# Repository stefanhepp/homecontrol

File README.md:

HomeControl
===========

This is the sourcecode and plans for my home automation system.

Content
=======

- `homecontrol`: Sources and schematics for a simple AtMega based home automation controller with 8 24VDC digital inputs, 8 24VDC digital outputs (open collector), RS232 and 2 230VAC sense inputs.
- `pixtend`: Sources for the main controller, based on an PiXtend v2-S with Raspberry 3B, written in Python. Connects via RS232 and MQTT to the network.

Installation Pixtend OS
=======================

- Install Raspbian OS (64bit)
   - `sudo rpi-imager`: Enable SSH, set hostname, username, password
- Setup Rasbian, install software
  ```
  # Enable SPI, UART, console bootup, set locale
  sudo raspi-config
  sudo apt install vim screen git gpiod libgpiod-dev python3-dev python3-pip python3-paho-mqtt
  ```
- Install Pixtend Python library
  ```
  git clone https://git.kontron-electronics.de/sw/ked/raspberry-pi/pixtend-v2/pplv2.git
  cd pplv2
  git checkout 0.1.6-dev
  python setup.py bdist_wheel
  # Install into venv
  python -m venv ~/.venv
  source ~/.venv/bin/activate
  pip install dist/pixtendlibv2-0.1.6-py3-none-any.whl
  ```
- Install pixcontrol script
  ```
  # Install prerequisites
  . ~/.venv/bin/activate
  pip install pyserial paho-mqtt
  cd ~/homecontrol/pixtend
  sudo cp pixcontrol.service /etc/systemd/system/
  sudo systemctl enable pixcontrol
  ```

License
=======

This program is free software: you can redistribute it and/or modify
it under the terms of the GNU General Public License as published by
the Free Software Foundation, either version 3 of the License, or
(at your option) any later version.

This program is distributed in the hope that it will be useful,
but WITHOUT ANY WARRANTY; without even the implied warranty of
MERCHANTABILITY or FITNESS FOR A PARTICULAR PURPOSE.  See the
GNU General Public License for more details.

You should have received a copy of the GNU General Public License
along with this program.  If not, see <https://www.gnu.org/licenses/>.

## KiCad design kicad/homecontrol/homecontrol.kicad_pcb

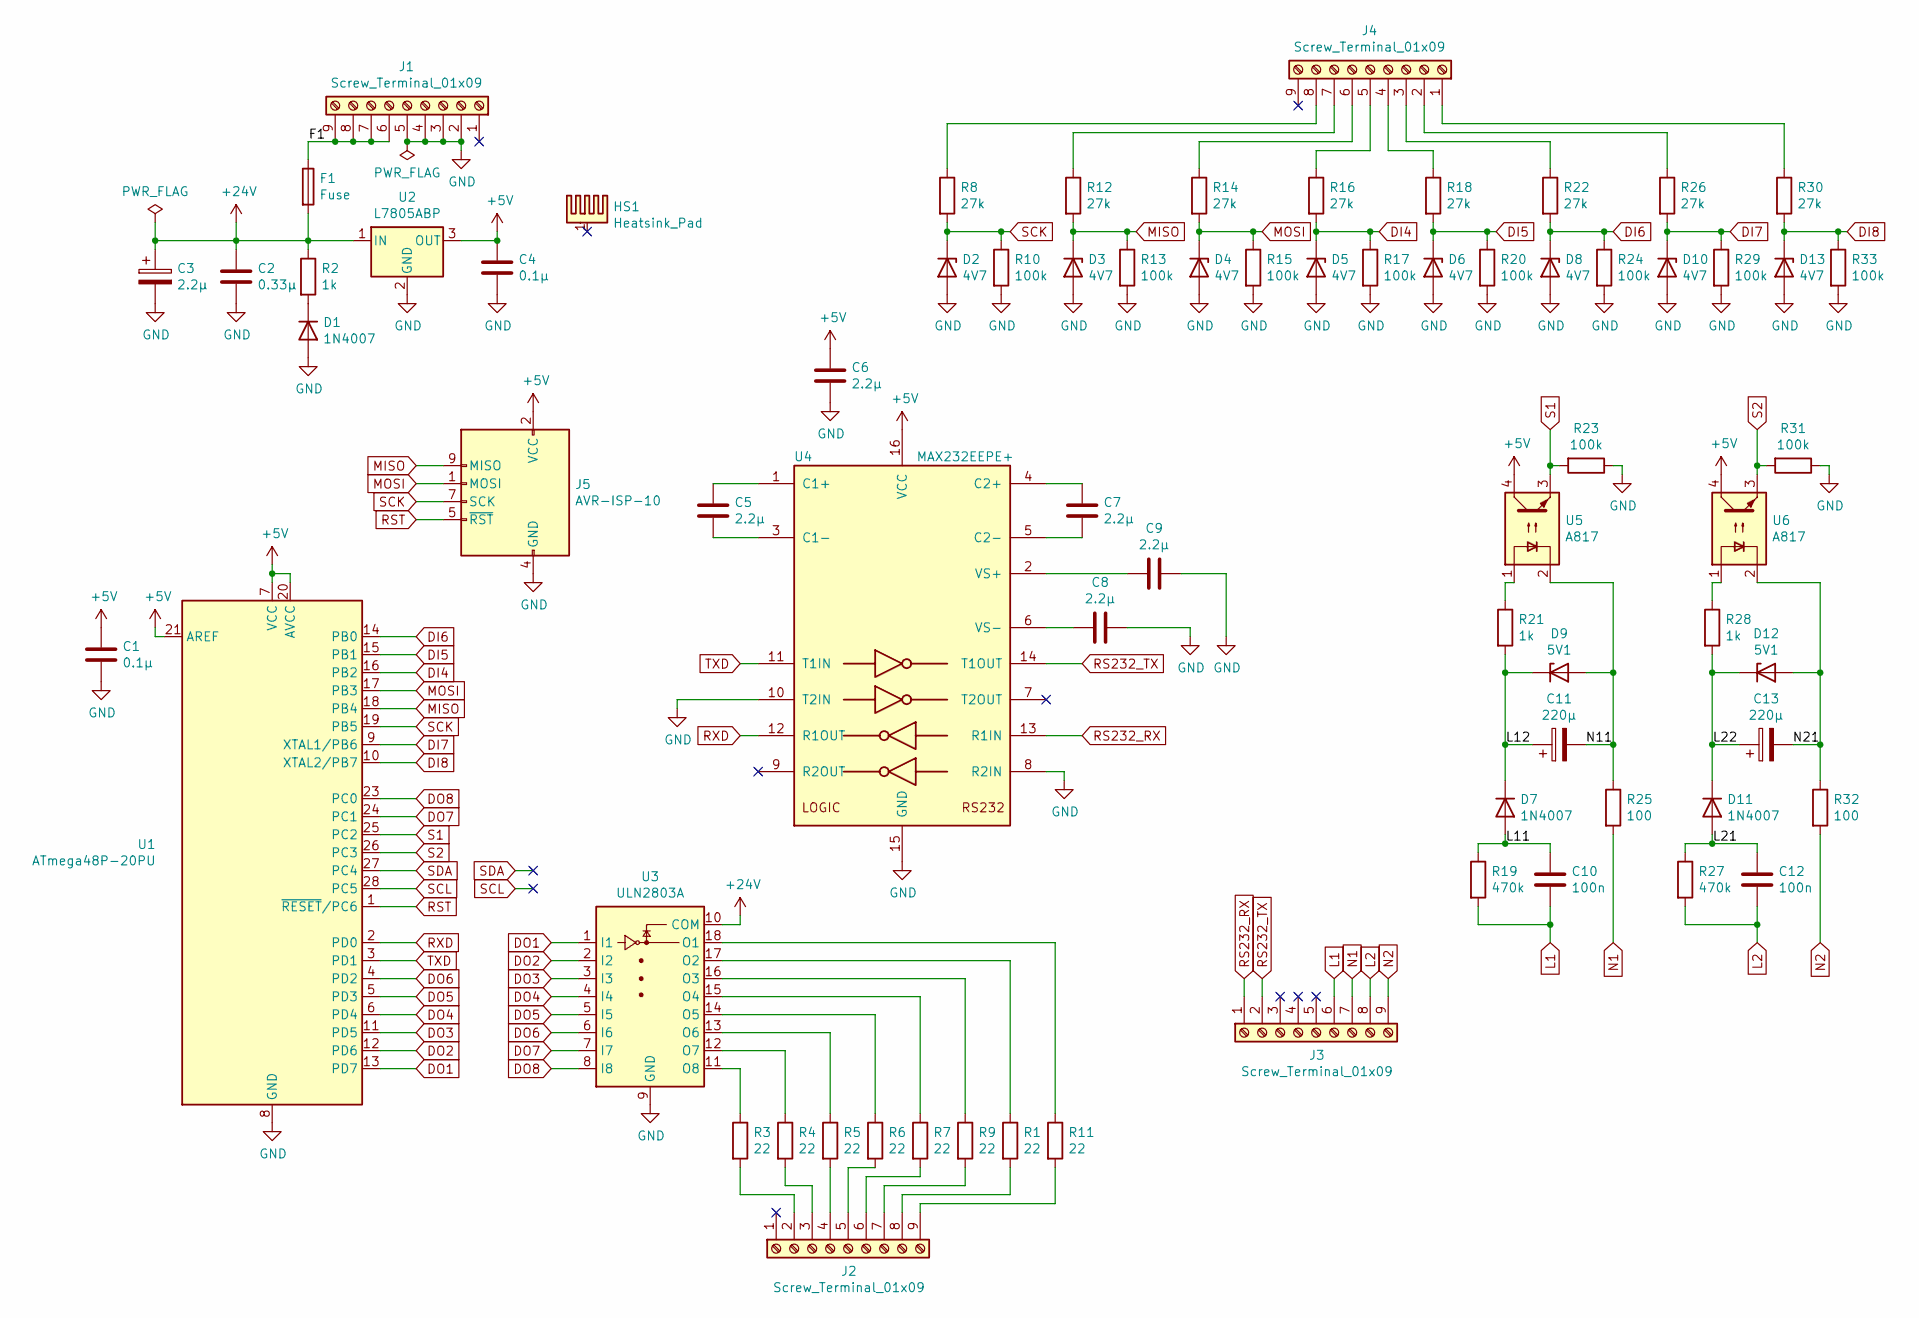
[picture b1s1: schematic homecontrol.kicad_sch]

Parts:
C1, C4: 0.1µ; C_Rect_L7.0mm_W2.5mm_P5.00mm; Voltage 50V
C2: 0.33µ; C_Disc_D4.7mm_W2.5mm_P5.00mm; Voltage 50V
C3: 2.2µ; CP_Radial_D6.3mm_P2.50mm; Voltage 50V
C5, C6, C7, C8, C9: 2.2µ; C_Rect_L4.6mm_W3.0mm_P2.50mm_MKS02_FKP02; Voltage 50V
C10, C12: 100n; C_Rect_L19.0mm_W6.0mm_P15.00mm_MKS4; Voltage 250V
C11, C13: 220µ; CP_Radial_D6.3mm_P2.50mm; Voltage 16V
D1: 1N4007; D_DO-35_SOD27_P2.54mm_Vertical_KathodeUp
D2, D3, D4, D5, D6, D8, D10, D13: 4V7; D_DO-35_SOD27_P2.54mm_Vertical_KathodeUp
D7, D11: 1N4007; D_DO-201AD_P3.81mm_Vertical_KathodeUp
D9, D12: 5V1; D_DO-35_SOD27_P2.54mm_Vertical_KathodeUp
F1: Fuse; Fuseholder_Cylinder-5x20mm_Schurter_0031_8201_Horizontal_Op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
HS1: Heatsink_Pad; Heatsink_Aavid_TO-220_H12.7mm
J1, J2, J3, J4: Screw_Terminal_01x09; TerminalBlock_Phoenix_MKDS-1,5-9-5.08_1x09_P5.08mm_Horizont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
J5: AVR-ISP-10; IDC-Header_2x05_P2.54mm_Vertical
R1, R3, R4, R5, R6, R7, R9, R11: 22; R_Axial_DIN0207_L6.3mm_D2.5mm_P2.54mm_Vertical
R2, R21, R28: 1k; R_Axial_DIN0207_L6.3mm_D2.5mm_P2.54mm_Vertical
R8, R12, R14, R16, R18, R22, R26, R30: 27k; R_Axial_DIN0207_L6.3mm_D2.5mm_P2.54mm_Vertical
R10, R13, R15, R17, R20, R23, R24, R29, R31, R33: 100k; R_Axial_DIN0207_L6.3mm_D2.5mm_P2.54mm_Vertical
R19, R27: 470k; R_Axial_DIN0207_L6.3mm_D2.5mm_P10.16mm_Horizontal
R25, R32: 100; R_Axial_DIN0207_L6.3mm_D2.5mm_P10.16mm_Horizontal
U1: ATmega48P-20PU; DIP-28_W7.62mm_Socket
U2: L7805ABP; TO-220-3_Vertical
U3: ULN2803A; DIP-18_W7.62mm_Socket
U4: MAX232EEPE+; DIP-16_W7.62mm_Socket
U5, U6: A817; DIP-4_W7.62mm

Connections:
+5V: C1.1, C4.1, C6.1, J5.2 (VCC), U1.7 (VCC), U1.20 (AVCC), U1.21 (AREF), U2.3 (OUT), U4.16 (VCC), U5.4, U6.4
+24V: C2.1, C3.1, F1.2, R2.1, U2.1 (IN), U3.10 (COM)
/F1: F1.1, J1.6, J1.7, J1.8, J1.9
/L11: C10.2, D7.2 (A), R19.1
/L12: C11.1, D7.1 (K), D9.1 (K), R21.2
/L21: C12.2, D11.2 (A), R27.1
/L22: C13.1, D11.1 (K), D12.1 (K), R28.2
/N11: C11.2, D9.2 (A), R25.1, U5.2
/N21: C13.2, D12.2 (A), R32.1, U6.2
DI4: D5.1 (K), R16.2, R17.1, U1.16 (PB2)
DI5: D6.1 (K), R18.2, R20.1, U1.15 (PB1)
DI6: D8.1 (K), R22.2, R24.1, U1.14 (PB0)
DI7: D10.1 (K), R26.2, R29.1, U1.9 (XTAL1/PB6)
DI8: D13.1 (K), R30.2, R33.1, U1.10 (XTAL2/PB7)
DO1: U1.13 (PD7), U3.1 (I1)
DO2: U1.12 (PD6), U3.2 (I2)
DO3: U1.11 (PD5), U3.3 (I3)
DO4: U1.6 (PD4), U3.4 (I4)
DO5: U1.5 (PD3), U3.5 (I5)
DO6: U1.4 (PD2), U3.6 (I6)
DO7: U1.24 (PC1), U3.7 (I7)
DO8: U1.23 (PC0), U3.8 (I8)
GND: C1.2, C2.2, C3.2, C4.2, C6.2, C8.1, C9.1, D1.2 (A), D2.2 (A), D3.2 (A), D4.2 (A), D5.2 (A), D6.2 (A), D8.2 (A), D10.2 (A), D13.2 (A), J1.2, J1.3, J1.4, J1.5, J5.4 (GND), J5.6 (GND), J5.8 (GND), J5.10 (GND), R10.2, R13.2, R15.2, R17.2, R20.2, R23.1, R24.2, R29.2, R31.1, R33.2, U1.8 (GND), U1.22 (GND), U2.2 (GND), U3.9 (GND), U4.8 (R2IN), U4.10 (T2IN), U4.15 (GND)
L1: C10.1, J3.6, R19.2
L2: C12.1, J3.8, R27.2
MISO: D3.1 (K), J5.9 (MISO), R12.2, R13.1, U1.18 (PB4)
MOSI: D4.1 (K), J5.1 (MOSI), R14.2, R15.1, U1.17 (PB3)
N1: J3.7, R25.2
N2: J3.9, R32.2
unnamed: D1.1 (K), R2.2
unnamed: J2.2, R3.2
unnamed: J2.3, R4.2
unnamed: J2.4, R5.2
unnamed: J2.5, R6.2
unnamed: J2.6, R7.2
unnamed: J2.7, R9.2
unnamed: J2.8, R1.2
unnamed: J2.9, R11.2
unnamed: J4.1, R30.1
unnamed: J4.2, R26.1
unnamed: J4.3, R22.1
unnamed: J4.4, R18.1
unnamed: J4.5, R16.1
unnamed: J4.6, R14.1
unnamed: J4.7, R12.1
unnamed: J4.8, R8.1
unnamed: R21.1, U5.1
unnamed: R28.1, U6.1
unnamed: R11.1, U3.18 (O1)
unnamed: R1.1, U3.17 (O2)
unnamed: R9.1, U3.16 (O3)
unnamed: R7.1, U3.15 (O4)
unnamed: R6.1, U3.14 (O5)
unnamed: R5.1, U3.13 (O6)
unnamed: R4.1, U3.12 (O7)
unnamed: R3.1, U3.11 (O8)
unnamed: C5.1, U4.1 (C1+)
unnamed: C5.2, U4.3 (C1-)
unnamed: C7.1, U4.4 (C2+)
unnamed: C7.2, U4.5 (C2-)
unnamed: C9.2, U4.2 (VS+)
unnamed: C8.2, U4.6 (VS-)
RS232_RX: J3.1, U4.13 (R1IN)
RS232_TX: J3.2, U4.14 (T1OUT)
RST: J5.5 (~RST), U1.1 (~RESET/PC6)
RXD: U1.2 (PD0), U4.12 (R1OUT)
S1: R23.2, U1.25 (PC2), U5.3
S2: R31.2, U1.26 (PC3), U6.3
SCK: D2.1 (K), J5.7 (SCK), R8.2, R10.1, U1.19 (PB5)
SCL: U1.28 (PC5)
SDA: U1.27 (PC4)
TXD: U1.3 (PD1), U4.11 (T1IN)

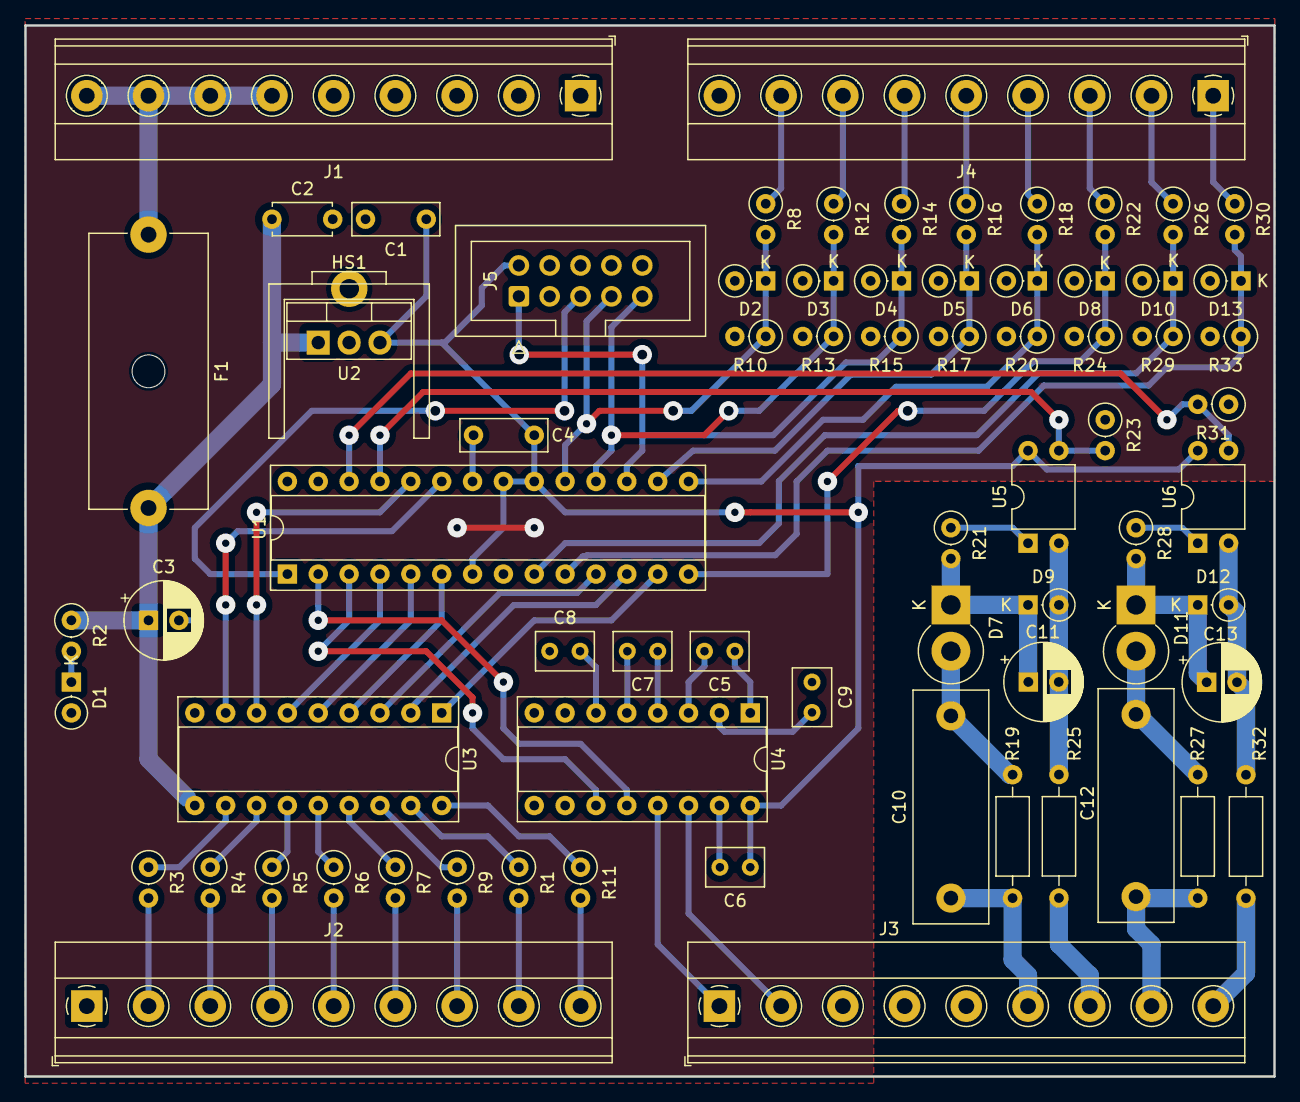
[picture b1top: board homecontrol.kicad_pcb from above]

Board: 2 copper layers, 102.8 x 86.5 mm, 72 parts (0 on the bottom side), 70 nets.

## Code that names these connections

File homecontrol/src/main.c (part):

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 *
 * Pinout:
 * - PortB:
 *   - PB0: DIn6
 *   - PB1: DIn5
 *   - PB2: DIn4 - Stair-Staircase
 *   - PB3: DIn3 - Stair-Light
 *   - PB4: DIn2 - Staircase
 *   - PB5: DIn1 - Livingroom
 *   - PB6: DIn7
 *   - PB7: DIn8
 * - PortC:
 *   - PC0: DOut1 - Livingroom
 *   - PC1: DOut2 - Staircase
 *   - PC2: Sense In 1 - Stair Sense
 *   - PC3: Sense In 2
 *   - PC4: SDA
 *   - PC5: SCL
 *   - PC6: Reset In
 * - PortD:
 *   - PD0: RXD
 *   - PD1: TXD
 *   - PD2: DOut3 - Stair-Light
 *   - PD3: DOut4 - Stair-Sense
 *   - PD4: DOut5
 *   - PD5: DOut6
 *   - PD6: DOut7
 *   - PD7: DOut8
 **/

// Define CPU clock speed and UART baud rate
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/**
 * IO Mapping
 **/
#define PB_DIN1 PB5
#define PB_DIN2 PB4
#define PB_DIN3 PB3
#define PB_DIN4 PB2
#define PB_DIN5 PB1
#define PB_DIN6 PB0
#define PB_DIN7 PB6
#define PB_DIN8 PB7

#define PC_SENSE1 PC2
#define PC_SENSE2 PC3

#define PC_DOUT1 PC0
#define PC_DOUT2 PC1
#define PD_DOUT3 PD2
#define PD_DOUT4 PD3
#define PD_DOUT5 PD4
#define PD_DOUT6 PD5
#define PD_DOUT7 PD6
#define PD_DOUT8 PD7

/**
 * UART command codes
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
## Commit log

2018-09-16 Basic control logic implemenation
2018-09-17 Added UART implementation
2018-09-23 Added timer for long presses, bugfixes. First working version.
2018-10-05 Changed livingroom switch from pushbutton to switch type
2018-10-05 Implemented blinking leds via PWM
2018-10-09 Implemented UART and MQTT control
2018-10-10 Fixed UART receive, turn off garden light on All Off.
2018-10-10 Added configurable All-Off timer and configurable pump timer intervals
2018-10-10 Added GPLv3 header
2018-10-10 Added readme
2019-06-01 Added some comments, reduced longpress time to 1.8s
2019-06-01 Added flash script for RaspberryPi avrdude
2019-06-20 Use stair sensor as switch instead of as button
2020-01-15 Changed second doorbell button to door open button
2021-05-16 Added KiCad Schematics for HomeControl
2021-05-16 Updated footprints and BOM
2021-05-17 First full PCB layout of HomeControl
2023-05-13 Updated HomeControl PCB to KiCAD 7.0, fixed MKS4 footprint
2023-05-14 Adapted IO mapping to new PCB layout
2023-05-14 Update flash script for Pololu ISP
2024-06-30 Fixed MQTT client implementation
2024-11-04 Auto-reset door light mode by timer
2025-09-10 Added install instructions for Pixtend software
2025-09-11 Fixes for python3, added installation instructions
2026-01-07 Disable tvroom lights with All-Off, fixes for Python 3
2026-04-18 Added MQTT script for Shelly dimmer

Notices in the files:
homecontrol/src/main.c:
Copyright 2018 Stefan Hepp
